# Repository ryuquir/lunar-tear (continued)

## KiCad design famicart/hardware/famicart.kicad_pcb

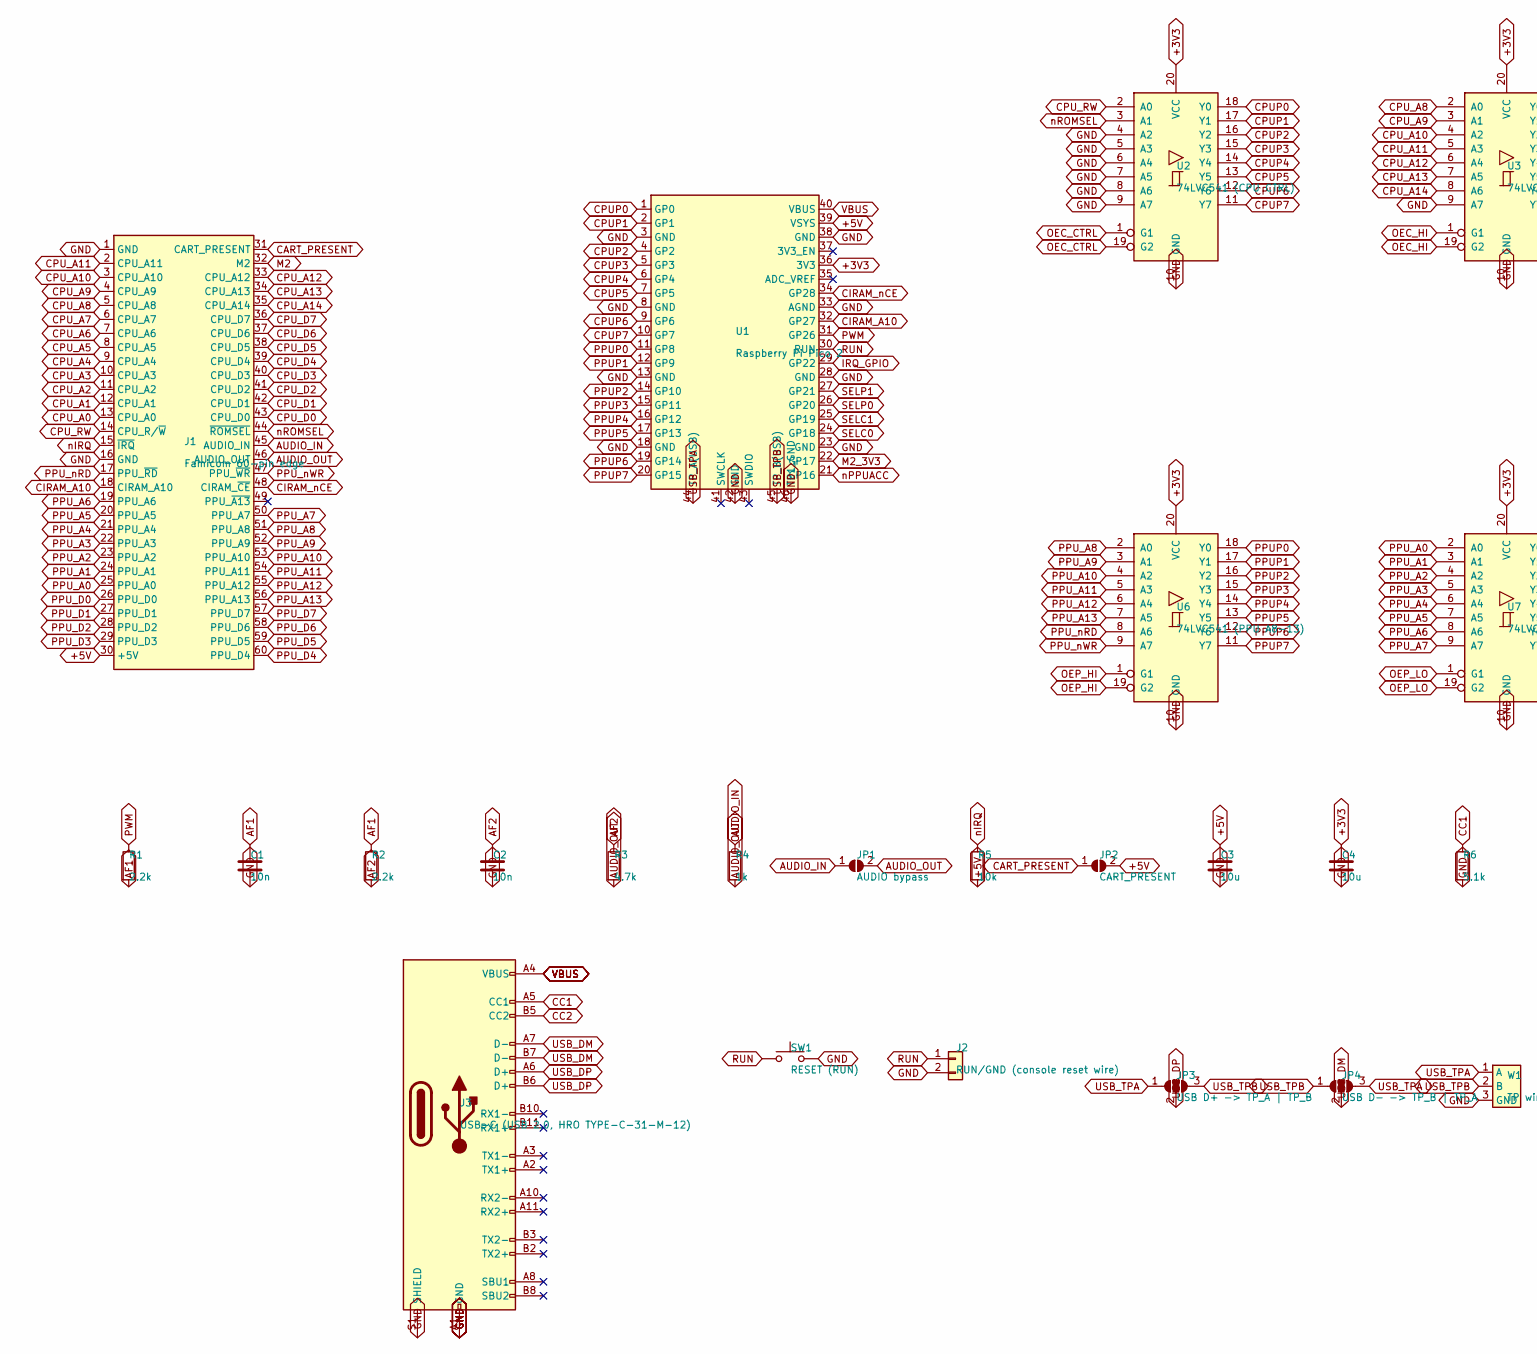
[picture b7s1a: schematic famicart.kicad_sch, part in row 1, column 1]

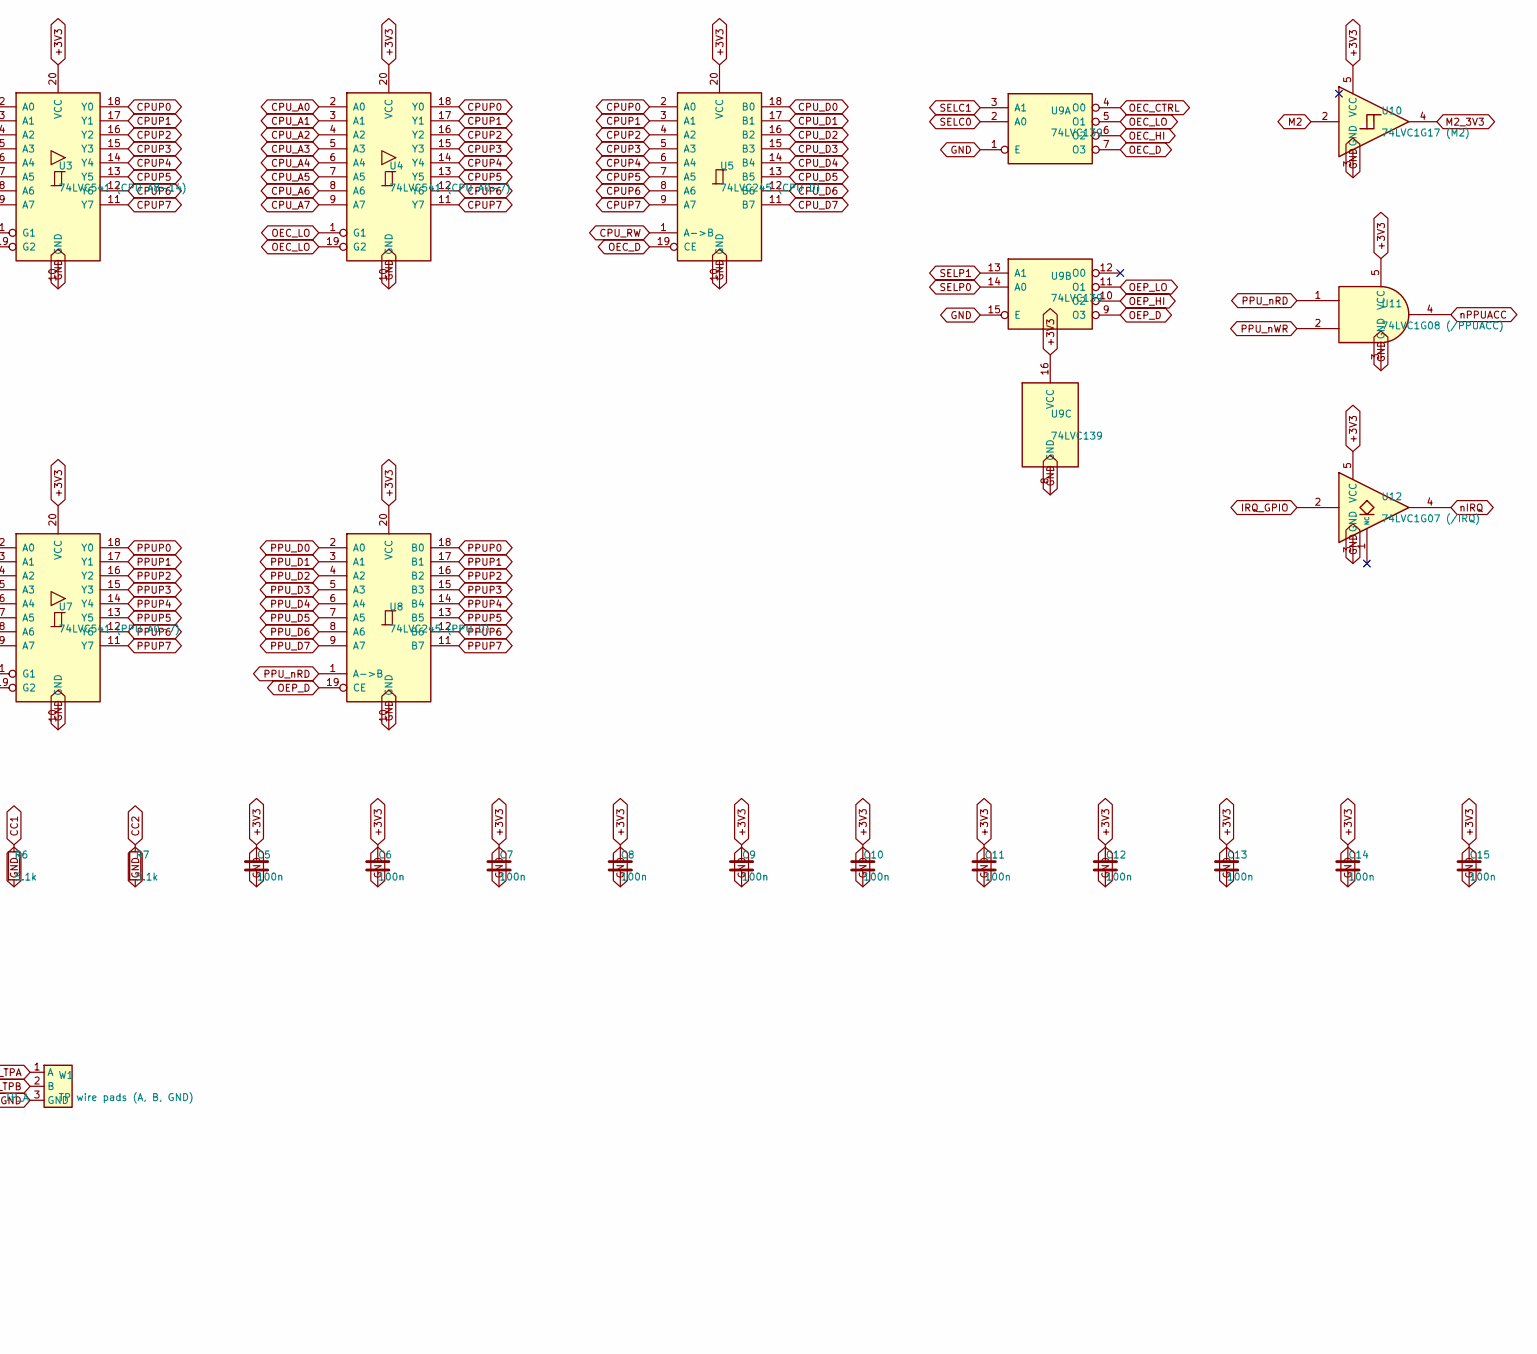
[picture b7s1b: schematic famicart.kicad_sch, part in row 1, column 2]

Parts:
C1, C2: 10n; C_0603_1608Metric
C3, C4: 10u; C_0805_2012Metric
C5, C6, C7, C8, C9, C10, C11, C12, C13, C14, C15: 100n; C_0603_1608Metric
J1: Famicom 60-pin edge; Famicom_CardEdge_60
J2: RUN/GND (console reset wire); PinHeader_1x02_P2.54mm_Vertical
J3: USB-C (USB 2.0, HRO TYPE-C-31-M-12); USB_C_Receptacle_HRO_TYPE-C-31-M-12
JP1: AUDIO bypass; SolderJumper-2_P1.3mm_Open_RoundedPad1.0x1.5mm
JP2: CART_PRESENT; SolderJumper-2_P1.3mm_Open_RoundedPad1.0x1.5mm
JP3: USB D+ -> TP_A | TP_B; SolderJumper-3_P1.6mm_Open
JP4: USB D- -> TP_B | TP_A; SolderJumper-3_P1.6mm_Open
R1, R2: 2.2k; R_0603_1608Metric
R3: 4.7k; R_0603_1608Metric
R4: 1k; R_0603_1608Metric
R5: 10k; R_0603_1608Metric
R6, R7: 5.1k; R_0603_1608Metric
SW1: RESET (RUN); SW_SPST_TL3342
U1: Raspberry Pi Pico 2; RPi_Pico_SMD
U2: 74LVC541 (CPU CTRL); TSSOP-20_4.4x6.5mm_P0.65mm
U3: 74LVC541 (CPU A8-14); TSSOP-20_4.4x6.5mm_P0.65mm
U4: 74LVC541 (CPU A0-7); TSSOP-20_4.4x6.5mm_P0.65mm
U5: 74LVC245 (CPU D); TSSOP-20_4.4x6.5mm_P0.65mm
U6: 74LVC541 (PPU A8-13); TSSOP-20_4.4x6.5mm_P0.65mm
U7: 74LVC541 (PPU A0-7); TSSOP-20_4.4x6.5mm_P0.65mm
U8: 74LVC245 (PPU D); TSSOP-20_4.4x6.5mm_P0.65mm
U9: 74LVC139; TSSOP-16_4.4x5mm_P0.65mm
U10: 74LVC1G17 (M2); SOT-23-5
U11: 74LVC1G08 (/PPUACC); SOT-23-5
U12: 74LVC1G07 (/IRQ); SOT-23-5
W1: TP wire pads (A, B, GND); WirePads_1x3

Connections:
+3V3: C4.1, C5.1, C6.1, C7.1, C8.1, C9.1, C10.1, C11.1, C12.1, C13.1, C14.1, C15.1, U1.36 (3V3), U2.20 (VCC), U3.20 (VCC), U4.20 (VCC), U5.20 (VCC), U6.20 (VCC), U7.20 (VCC), U8.20 (VCC), U9.16 (VCC), U10.5 (VCC), U11.5 (VCC), U12.5 (VCC)
+5V: C3.1, J1.30 (+5V), JP2.2 (B), R5.2, U1.39 (VSYS)
AF1: C1.1, R1.2, R2.1
AF2: C2.1, R2.2, R3.1
AUDIO_IN: J1.45 (AUDIO_IN), JP1.1 (A), R4.1
AUDIO_OUT: J1.46 (AUDIO_OUT), JP1.2 (B), R3.2, R4.2
CART_PRESENT: J1.31 (CART_PRESENT), JP2.1 (A)
CC1: J3.A5 (CC1), R6.1
CC2: J3.B5 (CC2), R7.1
CIRAM_A10: J1.18 (CIRAM_A10), U1.32 (GP27)
CIRAM_nCE: J1.48 (CIRAM_~CE), U1.34 (GP28)
CPUP0: U1.1 (GP0), U2.18 (Y0), U3.18 (Y0), U4.18 (Y0), U5.2 (A0)
CPUP1: U1.2 (GP1), U2.17 (Y1), U3.17 (Y1), U4.17 (Y1), U5.3 (A1)
CPUP2: U1.4 (GP2), U2.16 (Y2), U3.16 (Y2), U4.16 (Y2), U5.4 (A2)
CPUP3: U1.5 (GP3), U2.15 (Y3), U3.15 (Y3), U4.15 (Y3), U5.5 (A3)
CPUP4: U1.6 (GP4), U2.14 (Y4), U3.14 (Y4), U4.14 (Y4), U5.6 (A4)
CPUP5: U1.7 (GP5), U2.13 (Y5), U3.13 (Y5), U4.13 (Y5), U5.7 (A5)
CPUP6: U1.9 (GP6), U2.12 (Y6), U3.12 (Y6), U4.12 (Y6), U5.8 (A6)
CPUP7: U1.10 (GP7), U2.11 (Y7), U3.11 (Y7), U4.11 (Y7), U5.9 (A7)
CPU_A0: J1.13 (CPU_A0), U4.2 (A0)
CPU_A1: J1.12 (CPU_A1), U4.3 (A1)
CPU_A2: J1.11 (CPU_A2), U4.4 (A2)
CPU_A3: J1.10 (CPU_A3), U4.5 (A3)
CPU_A4: J1.9 (CPU_A4), U4.6 (A4)
CPU_A5: J1.8 (CPU_A5), U4.7 (A5)
CPU_A6: J1.7 (CPU_A6), U4.8 (A6)
CPU_A7: J1.6 (CPU_A7), U4.9 (A7)
CPU_A8: J1.5 (CPU_A8), U3.2 (A0)
CPU_A9: J1.4 (CPU_A9), U3.3 (A1)
CPU_A10: J1.3 (CPU_A10), U3.4 (A2)
CPU_A11: J1.2 (CPU_A11), U3.5 (A3)
CPU_A12: J1.33 (CPU_A12), U3.6 (A4)
CPU_A13: J1.34 (CPU_A13), U3.7 (A5)
CPU_A14: J1.35 (CPU_A14), U3.8 (A6)
CPU_D0: J1.43 (CPU_D0), U5.18 (B0)
CPU_D1: J1.42 (CPU_D1), U5.17 (B1)
CPU_D2: J1.41 (CPU_D2), U5.16 (B2)
CPU_D3: J1.40 (CPU_D3), U5.15 (B3)
CPU_D4: J1.39 (CPU_D4), U5.14 (B4)
CPU_D5: J1.38 (CPU_D5), U5.13 (B5)
CPU_D6: J1.37 (CPU_D6), U5.12 (B6)
CPU_D7: J1.36 (CPU_D7), U5.11 (B7)
CPU_RW: J1.14 (CPU_R/~W), U2.2 (A0), U5.1 (A->B)
GND: C1.2, C2.2, C3.2, C4.2, C5.2, C6.2, C7.2, C8.2, C9.2, C10.2, C11.2, C12.2, C13.2, C14.2, C15.2, J1.1 (GND), J1.16 (GND), J2.2, J3.A1 (GND), J3.A12 (GND), J3.B1 (GND), J3.B12 (GND), J3.S1 (SHIELD), R6.2, R7.2, SW1.2, U1.3 (GND), U1.8 (GND), U1.13 (GND), U1.18 (GND), U1.23 (GND), U1.28 (GND), U1.33 (AGND), U1.38 (GND), U1.42 (GND), U1.46 (TP1_GND), U2.4 (A2), U2.5 (A3), U2.6 (A4), U2.7 (A5), U2.8 (A6), U2.9 (A7), U2.10 (GND), U3.9 (A7), U3.10 (GND), U4.10 (GND), U5.10 (GND), U6.10 (GND), U7.10 (GND), U8.10 (GND), U9.1 (E), U9.8 (GND), U9.15 (E), U10.3 (GND), U11.3 (GND), U12.3 (GND), W1.3 (GND)
IRQ_GPIO: U1.29 (GP22), U12.2
M2: J1.32 (M2), U10.2
M2_3V3: U1.22 (GP17), U10.4
OEC_CTRL: U2.1 (G1), U2.19 (G2), U9.4 (O0)
OEC_D: U5.19 (CE), U9.7 (O3)
OEC_HI: U3.1 (G1), U3.19 (G2), U9.6 (O2)
OEC_LO: U4.1 (G1), U4.19 (G2), U9.5 (O1)
OEP_D: U8.19 (CE), U9.9 (O3)
OEP_HI: U6.1 (G1), U6.19 (G2), U9.10 (O2)
OEP_LO: U7.1 (G1), U7.19 (G2), U9.11 (O1)
PPUP0: U1.11 (GP8), U6.18 (Y0), U7.18 (Y0), U8.18 (B0)
PPUP1: U1.12 (GP9), U6.17 (Y1), U7.17 (Y1), U8.17 (B1)
PPUP2: U1.14 (GP10), U6.16 (Y2), U7.16 (Y2), U8.16 (B2)
PPUP3: U1.15 (GP11), U6.15 (Y3), U7.15 (Y3), U8.15 (B3)
PPUP4: U1.16 (GP12), U6.14 (Y4), U7.14 (Y4), U8.14 (B4)
PPUP5: U1.17 (GP13), U6.13 (Y5), U7.13 (Y5), U8.13 (B5)
PPUP6: U1.19 (GP14), U6.12 (Y6), U7.12 (Y6), U8.12 (B6)
PPUP7: U1.20 (GP15), U6.11 (Y7), U7.11 (Y7), U8.11 (B7)
PPU_A0: J1.25 (PPU_A0), U7.2 (A0)
PPU_A1: J1.24 (PPU_A1), U7.3 (A1)
PPU_A2: J1.23 (PPU_A2), U7.4 (A2)
PPU_A3: J1.22 (PPU_A3), U7.5 (A3)
PPU_A4: J1.21 (PPU_A4), U7.6 (A4)
PPU_A5: J1.20 (PPU_A5), U7.7 (A5)
PPU_A6: J1.19 (PPU_A6), U7.8 (A6)
PPU_A7: J1.50 (PPU_A7), U7.9 (A7)
PPU_A8: J1.51 (PPU_A8), U6.2 (A0)
PPU_A9: J1.52 (PPU_A9), U6.3 (A1)
PPU_A10: J1.53 (PPU_A10), U6.4 (A2)
PPU_A11: J1.54 (PPU_A11), U6.5 (A3)
PPU_A12: J1.55 (PPU_A12), U6.6 (A4)
PPU_A13: J1.56 (PPU_A13), U6.7 (A5)
PPU_D0: J1.26 (PPU_D0), U8.2 (A0)
PPU_D1: J1.27 (PPU_D1), U8.3 (A1)
PPU_D2: J1.28 (PPU_D2), U8.4 (A2)
PPU_D3: J1.29 (PPU_D3), U8.5 (A3)
PPU_D4: J1.60 (PPU_D4), U8.6 (A4)
PPU_D5: J1.59 (PPU_D5), U8.7 (A5)
PPU_D6: J1.58 (PPU_D6), U8.8 (A6)
PPU_D7: J1.57 (PPU_D7), U8.9 (A7)
PPU_nRD: J1.17 (PPU_~RD), U6.8 (A6), U8.1 (A->B), U11.1
PPU_nWR: J1.47 (PPU_~WR), U6.9 (A7), U11.2
PWM: R1.1, U1.31 (GP26)
RUN: J2.1, SW1.1, U1.30 (RUN)
SELC0: U1.24 (GP18), U9.2 (A0)
SELC1: U1.25 (GP19), U9.3 (A1)
SELP0: U1.26 (GP20), U9.14 (A0)
SELP1: U1.27 (GP21), U9.13 (A1)
USB_DM: J3.A7 (D-), J3.B7 (D-), JP4.2 (C)
USB_DP: J3.A6 (D+), J3.B6 (D+), JP3.2 (C)
USB_TPA: JP3.1 (A), JP4.3 (B), U1.44 (TP_A(USB)), W1.1 (A)
USB_TPB: JP3.3 (B), JP4.1 (A), U1.45 (TP_B(USB)), W1.2 (B)
VBUS: J3.A4 (VBUS), J3.A9 (VBUS), J3.B4 (VBUS), J3.B9 (VBUS), U1.40 (VBUS)
nIRQ: J1.15 (~IRQ), R5.1, U12.4
nPPUACC: U1.21 (GP16), U11.4
nROMSEL: J1.44 (~ROMSEL), U2.3 (A1)

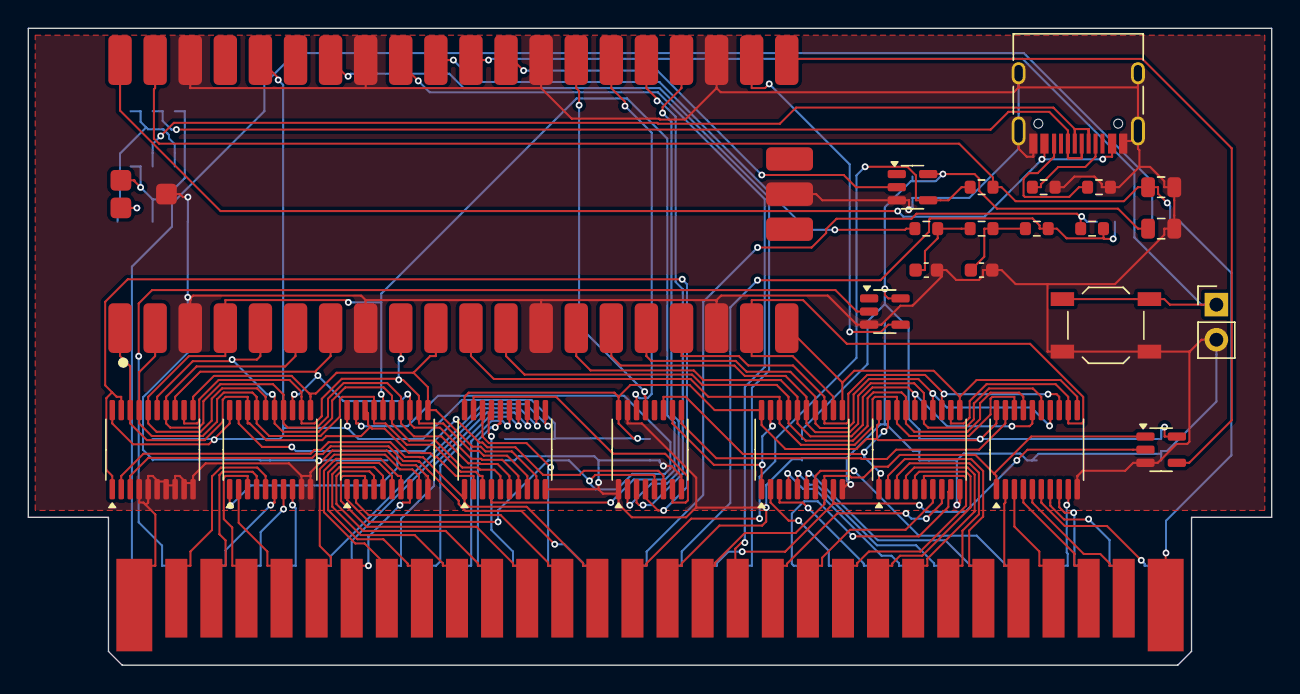
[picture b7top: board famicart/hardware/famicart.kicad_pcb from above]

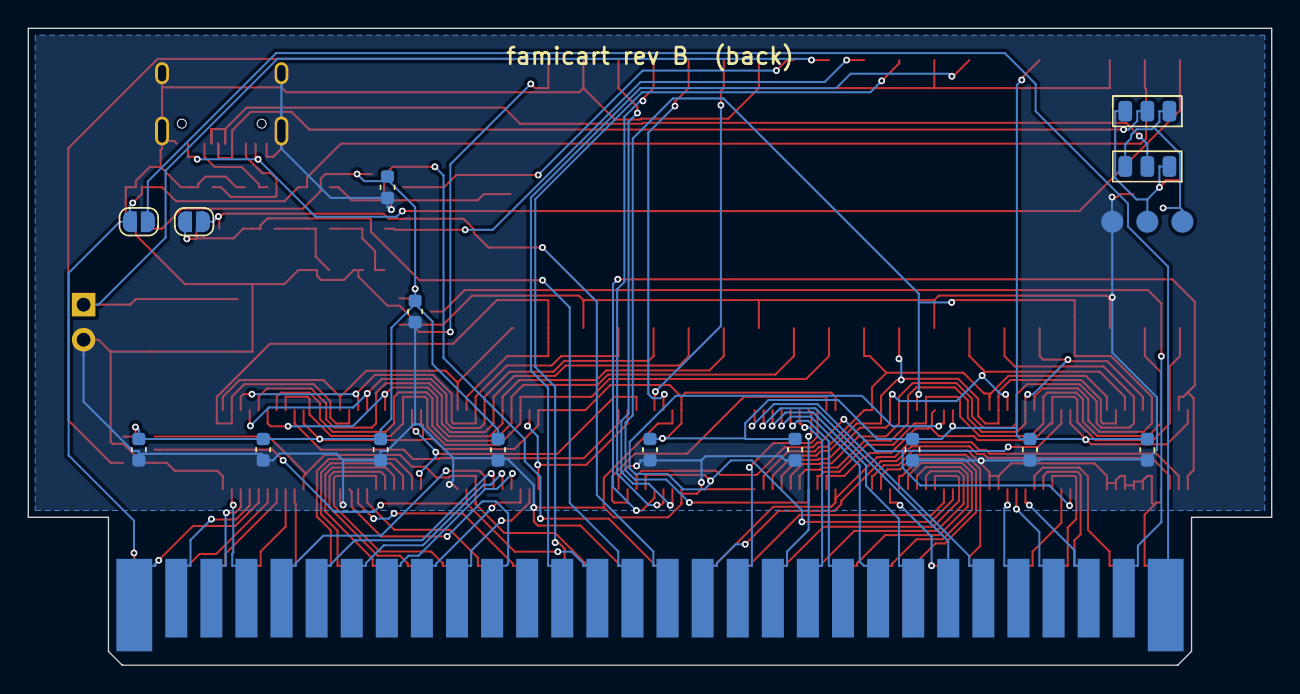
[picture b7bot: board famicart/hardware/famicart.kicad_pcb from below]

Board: 2 copper layers, 90.0 x 46.1 mm, 43 parts (16 on the bottom side), 100 nets.

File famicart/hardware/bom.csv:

Qty,Value,Footprint,References,Suggested part
1,Famicom 60-pin edge,Famicom_CardEdge_60,J1,"PCB card edge (gold fingers), no part"
1,Raspberry Pi Pico 2,RPi_Pico_SMD,U1,Raspberry Pi SC1631 (Pico 2) / Pico (RP2040) also fits
5,74LVC541,TSSOP-20_4.4x6.5mm_P0.65mm,U2 U3 U4 U6 U7,Nexperia 74LVC541APW (TSSOP-20)
2,74LVC245,TSSOP-20_4.4x6.5mm_P0.65mm,U5 U8,Nexperia 74LVC245APW (TSSOP-20)
1,74LVC139,TSSOP-16_4.4x5mm_P0.65mm,U9,Nexperia 74LVC139PW (TSSOP-16)
1,74LVC1G17,SOT-23-5,U10,Nexperia 74LVC1G17GW / TI SN74LVC1G17DBV
1,USB-C,USB_C_Receptacle_HRO_TYPE-C-31-M-12,J3,HRO TYPE-C-31-M-12 (16-pin USB 2.0 receptacle) or GCT USB4105-GF-A
2,5.1k,R_0603_1608Metric,R6 R7,0603 1% (USB-C CC pull-down)
1,USB D+ -> TP_A | TP_B,SolderJumper-3_P1.6mm_Open,JP3,"solder jumper, bridge after checking TP2/TP3"
1,USB D- -> TP_B | TP_A,SolderJumper-3_P1.6mm_Open,JP4,"solder jumper, bridge after checking TP2/TP3"
1,TP wire pads,WirePads_1x3,W1,no part (solder wires from Pico TP2/TP3/TP1 if hand-assembling)
1,RESET,SW_SPST_TL3342,SW1,E-Switch TL3342 / any 4.7x3.5 mm low-profile tactile
1,RUN/GND,PinHeader_1x02_P2.54mm_Vertical,J2,"2-pin 2.54 mm header (optional, wire to the console reset switch)"
1,74LVC1G08,SOT-23-5,U11,Nexperia 74LVC1G08GW / TI SN74LVC1G08DBV
1,74LVC1G07,SOT-23-5,U12,Nexperia 74LVC1G07GW / TI SN74LVC1G07DBV
2,2.2k,R_0603_1608Metric,R1 R2,0603 1%
1,4.7k,R_0603_1608Metric,R3,0603 1%
1,1k,R_0603_1608Metric,R4,0603 1%
1,10k,R_0603_1608Metric,R5,0603 1%
2,10n,C_0603_1608Metric,C1 C2,X7R 0603 50V
2,10u,C_0805_2012Metric,C3 C4,X5R 0805 10V
1,AUDIO bypass,SolderJumper-2_P1.3mm_Open_RoundedPad1.0x1.5mm,JP1,
1,CART_PRESENT,SolderJumper-2_P1.3mm_Open_RoundedPad1.0x1.5mm,JP2,
11,100n,C_0603_1608Metric,C5 C6 C7 C8 C9 C10 C11 C12 C13 C14 C15,X7R 0603 16V

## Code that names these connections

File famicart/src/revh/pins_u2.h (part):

/* Generated by tools/fw/gen_revh_pins.py from tools/pcb/design_revh.py -- do not edit; run the script again.
 * famicart rev H, U2: PPU bus (CHR, nametables, PPU write capture; PEV to U3).
 * RP2350B (QFN-80) with U12 (W25Q128JVSIQ, 16 MB) on QSPI CS0, its own 12 MHz crystal, LED D22 on LED2.
 * SWCLK (pin 33) SWCLK2, SWDIO (pin 34) SWDIO2, RUN (pin 35) nRST, USB pins 66 / 67 open.
 * "pin" below is the QFN-80 pin (design_revd.GPIO_PIN, checked against the datasheet). Include exactly one
 * pins_u<N>.h per program: the names repeat across chips with other numbers. */
#ifndef FAMICART_REVH_PINS_U2_H
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#define REVH_IS_HUB 0

/* ---- every connected GPIO: pin, net, what else is on the net */
#define PIN_PA0       0  /* pin 77  PA0: U5; RN10 1k -> PPU_A0 (finger 25) */
#define PIN_PA1       1  /* pin 78  PA1: U5; RN9 1k -> PPU_A1 (finger 24) */
#define PIN_PA2       2  /* pin 79  PA2: U5; RN9 1k -> PPU_A2 (finger 23) */
#define PIN_PA3       3  /* pin 80  PA3: U5; RN8 1k -> PPU_A3 (finger 22) */
#define PIN_PA4       4  /* pin  1  PA4: U5; RN8 1k -> PPU_A4 (finger 21) */
#define PIN_PA5       5  /* pin  2  PA5: U5; RN7 1k -> PPU_A5 (finger 20) */
#define PIN_PA6       6  /* pin  3  PA6: U5; RN7 1k -> PPU_A6 (finger 19) */
#define PIN_PA7       7  /* pin  4  PA7: U5; RN8 1k -> PPU_A7 (finger 50) */
#define PIN_PA8       8  /* pin  6  PA8: U5; RN8 1k -> PPU_A8 (finger 51) */
#define PIN_PA9       9  /* pin  7  PA9: U5; RN9 1k -> PPU_A9 (finger 52) */
#define PIN_PA10     10  /* pin  8  PA10: U3 U5; RN9 1k -> PPU_A10 (finger 53) */
#define PIN_PA11     11  /* pin  9  PA11: U3 U5; RN10 1k -> PPU_A11 (finger 54) */
#define PIN_PA12     12  /* pin 11  PA12: U3 U5; RN10 1k -> PPU_A12 (finger 55) */
#define PIN_PA13     13  /* pin 12  PA13: U3 U5; RN10 1k -> PPU_A13 (finger 56) */
#define PIN_PD0      14  /* pin 13  PD0: RN11 680 x2 -> PPU_D0 (finger 26) */
#define PIN_PD1      15  /* pin 14  PD1: RN11 680 x2 -> PPU_D1 (finger 27) */
#define PIN_PD2      16  /* pin 16  PD2: RN12 680 x2 -> PPU_D2 (finger 28) */
#define PIN_PD3      17  /* pin 17  PD3: RN12 680 x2 -> PPU_D3 (finger 29) */
#define PIN_PD4      18  /* pin 18  PD4: RN16 680 x2 -> PPU_D4 (finger 60) */
#define PIN_PD5      19  /* pin 19  PD5: RN16 680 x2 -> PPU_D5 (finger 59) */
#define PIN_PD6      20  /* pin 20  PD6: RN15 680 x2 -> PPU_D6 (finger 58) */
#define PIN_PD7      21  /* pin 21  PD7: RN15 680 x2 -> PPU_D7 (finger 57) */
#define PIN_RD_D     22  /* pin 22  RD_D: U5; RN17 1k -> PPU_nRD (finger 17) */
#define PIN_PEV      23  /* pin 23  PEV: U3 */
#define PIN_P_WE     24  /* pin 25  P_WE: U5; RN32 1k -> PPU_nWE (finger 47) */
#define PIN_PWS_D    26  /* pin 27  PWS_D: U5; R28 2.2k -> +3V3; R29 2.2k -> +3V3; Q6 drain (gate PWE_G) */
#define PIN_PLINK_B  27  /* pin 28  PLINK_B: RN26 1k x2 -> PLINK_F */
#define PIN_LINK_B   28  /* pin 36  LINK_B: RN22 1k x4 -> LINK */
#define PIN_WL_CK    29  /* pin 37  WL_CK: U1 U5 U6 */
#define PIN_WL_D0    30  /* pin 38  WL_D0: U1 U5 U6 */
#define PIN_WL_D1    31  /* pin 39  WL_D1: U1 U5 U6 */
#define PIN_XH2_2_CK 32  /* pin 40  XH2_2_CK: U6 */
#define PIN_XH2_2_D0 33  /* pin 42  XH2_2_D0: U6 */
#define PIN_XH2_2_D1 34  /* pin 43  XH2_2_D1: U6 */
#define PIN_XH2_H_CK 35  /* pin 44  XH2_H_CK: U6 */
#define PIN_XH2_H_D0 36  /* pin 45  XH2_H_D0: U6 */
#define PIN_XH2_H_D1 37  /* pin 46  XH2_H_D1: U6 */
#define PIN_X25_2_CK 38  /* pin 47  X25_2_CK: U5 */
#define PIN_X25_2_D0 39  /* pin 48  X25_2_D0: U5 */
#define PIN_X25_2_D1 40  /* pin 49  X25_2_D1: U5 */
#define PIN_X25_5_CK 41  /* pin 52  X25_5_CK: U5 */
#define PIN_X25_5_D0 42  /* pin 53  X25_5_D0: U5 */
#define PIN_X25_5_D1 43  /* pin 54  X25_5_D1: U5 */
#define PIN_VSEL_S   44  /* pin 55  VSEL_S: all other chips; R35 100k -> GND; Q7 gate (drain VSEL_D) */
#define PIN_LED2     45  /* pin 56  LED2: R4 2.2k -> LED2_A */

/* ---- GPIOs with no net (reset state: input buffer off, pad pull-down, isolated): 25, 46, 47 */
#define REVH_UNCONNECTED_MASK 0xc00002000000ull
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
/* ---- consecutive groups for PIO programs (in / out / set / side-set base and count). The PIO window is the
 * GPIOBASE (0 or 16) whose 32 GPIOs hold the whole group; with GPIOBASE 16, `wait gpio` numbers are relative. */
/* PPU_BUS: PA0..RD_D, PPU bus capture: A0-13, D0-7, /RD; PIO window GPIOBASE 0 */
#define PIN_PPU_BUS_BASE  0
#define PIN_PPU_BUS_COUNT 23
_Static_assert(PIN_PA0 == PIN_PPU_BUS_BASE + 0 && PIN_PA1 == PIN_PPU_BUS_BASE + 1 &&
               PIN_PA2 == PIN_PPU_BUS_BASE + 2 && PIN_PA3 == PIN_PPU_BUS_BASE + 3 &&
               PIN_PA4 == PIN_PPU_BUS_BASE + 4 && PIN_PA5 == PIN_PPU_BUS_BASE + 5 &&
               PIN_PA6 == PIN_PPU_BUS_BASE + 6 && PIN_PA7 == PIN_PPU_BUS_BASE + 7 &&
               PIN_PA8 == PIN_PPU_BUS_BASE + 8 && PIN_PA9 == PIN_PPU_BUS_BASE + 9 &&
               PIN_PA10 == PIN_PPU_BUS_BASE + 10 && PIN_PA11 == PIN_PPU_BUS_BASE + 11 &&
               PIN_PA12 == PIN_PPU_BUS_BASE + 12 && PIN_PA13 == PIN_PPU_BUS_BASE + 13 &&
               PIN_PD0 == PIN_PPU_BUS_BASE + 14 && PIN_PD1 == PIN_PPU_BUS_BASE + 15 &&
               PIN_PD2 == PIN_PPU_BUS_BASE + 16 && PIN_PD3 == PIN_PPU_BUS_BASE + 17 &&
               PIN_PD4 == PIN_PPU_BUS_BASE + 18 && PIN_PD5 == PIN_PPU_BUS_BASE + 19 &&
               PIN_PD6 == PIN_PPU_BUS_BASE + 20 && PIN_PD7 == PIN_PPU_BUS_BASE + 21 &&
               PIN_RD_D == PIN_PPU_BUS_BASE + 22,
               "PPU_BUS: PA0..RD_D must be consecutive GPIOs");
/* PA: PA0..PA13, to PPU_A0..PPU_A13 through RN7, RN8, RN9, RN10 (1k each); PIO window GPIOBASE 0 */
#define PIN_PA_BASE  0
#define PIN_PA_COUNT 14
_Static_assert(PIN_PA0 == PIN_PA_BASE + 0 && PIN_PA1 == PIN_PA_BASE + 1 && PIN_PA2 == PIN_PA_BASE + 2 &&
               PIN_PA3 == PIN_PA_BASE + 3 && PIN_PA4 == PIN_PA_BASE + 4 && PIN_PA5 == PIN_PA_BASE + 5 &&
               PIN_PA6 == PIN_PA_BASE + 6 && PIN_PA7 == PIN_PA_BASE + 7 && PIN_PA8 == PIN_PA_BASE + 8 &&
               PIN_PA9 == PIN_PA_BASE + 9 && PIN_PA10 == PIN_PA_BASE + 10 && PIN_PA11 == PIN_PA_BASE + 11 &&
               PIN_PA12 == PIN_PA_BASE + 12 && PIN_PA13 == PIN_PA_BASE + 13,
               "PA: PA0..PA13 must be consecutive GPIOs");
/* PD: PD0..PD7, to PPU_D0..PPU_D7 through RN11, RN12, RN15, RN16 (680 x2 each); PIO window GPIOBASE 0 */
#define PIN_PD_BASE  14
#define PIN_PD_COUNT 8
_Static_assert(PIN_PD0 == PIN_PD_BASE + 0 && PIN_PD1 == PIN_PD_BASE + 1 && PIN_PD2 == PIN_PD_BASE + 2 &&
               PIN_PD3 == PIN_PD_BASE + 3 && PIN_PD4 == PIN_PD_BASE + 4 && PIN_PD5 == PIN_PD_BASE + 5 &&
               PIN_PD6 == PIN_PD_BASE + 6 && PIN_PD7 == PIN_PD_BASE + 7,
               "PD: PD0..PD7 must be consecutive GPIOs");
/* WL: WL_CK..WL_D1, WLINK received by this chip (U1 drives clock, data 0, data 1); PIO window GPIOBASE 0 or 16 */
#define PIN_WL_BASE  29
#define PIN_WL_COUNT 3
_Static_assert(PIN_WL_CK == PIN_WL_BASE + 0 && PIN_WL_D0 == PIN_WL_BASE + 1 && PIN_WL_D1 == PIN_WL_BASE + 2,
               "WL: WL_CK..WL_D1 must be consecutive GPIOs");
/* XH2_2: XH2_2_CK..XH2_2_D1, XLINK-H2 sent by this chip (U2 drives clock, data 0, data 1); PIO window GPIOBASE 16 */
#define PIN_XH2_2_BASE  32
#define PIN_XH2_2_COUNT 3
_Static_assert(PIN_XH2_2_CK == PIN_XH2_2_BASE + 0 && PIN_XH2_2_D0 == PIN_XH2_2_BASE + 1 &&
               PIN_XH2_2_D1 == PIN_XH2_2_BASE + 2,
               "XH2_2: XH2_2_CK..XH2_2_D1 must be consecutive GPIOs");
#define PIN_XH2_TX_BASE  PIN_XH2_2_BASE
#define PIN_XH2_TX_COUNT PIN_XH2_2_COUNT
/* XH2_H: XH2_H_CK..XH2_H_D1, XLINK-H2 received by this chip (U6 drives clock, data 0, data 1); PIO window GPIOBASE 16 */
#define PIN_XH2_H_BASE  35
#define PIN_XH2_H_COUNT 3
_Static_assert(PIN_XH2_H_CK == PIN_XH2_H_BASE + 0 && PIN_XH2_H_D0 == PIN_XH2_H_BASE + 1 &&
               PIN_XH2_H_D1 == PIN_XH2_H_BASE + 2,
               "XH2_H: XH2_H_CK..XH2_H_D1 must be consecutive GPIOs");
#define PIN_XH2_RX_BASE  PIN_XH2_H_BASE
#define PIN_XH2_RX_COUNT PIN_XH2_H_COUNT
/* X25_2: X25_2_CK..X25_2_D1, XLINK-25 sent by this chip (U2 drives clock, data 0, data 1); PIO window GPIOBASE 16 */
#define PIN_X25_2_BASE  38
#define PIN_X25_2_COUNT 3
_Static_assert(PIN_X25_2_CK == PIN_X25_2_BASE + 0 && PIN_X25_2_D0 == PIN_X25_2_BASE + 1 &&
               PIN_X25_2_D1 == PIN_X25_2_BASE + 2,
               "X25_2: X25_2_CK..X25_2_D1 must be consecutive GPIOs");
#define PIN_X25_TX_BASE  PIN_X25_2_BASE
#define PIN_X25_TX_COUNT PIN_X25_2_COUNT
/* X25_5: X25_5_CK..X25_5_D1, XLINK-25 received by this chip (U5 drives clock, data 0, data 1); PIO window GPIOBASE 16 */
#define PIN_X25_5_BASE  41
#define PIN_X25_5_COUNT 3
_Static_assert(PIN_X25_5_CK == PIN_X25_5_BASE + 0 && PIN_X25_5_D0 == PIN_X25_5_BASE + 1 &&
               PIN_X25_5_D1 == PIN_X25_5_BASE + 2,
               "X25_5: X25_5_CK..X25_5_D1 must be consecutive GPIOs");
#define PIN_X25_RX_BASE  PIN_X25_5_BASE
#define PIN_X25_RX_COUNT PIN_X25_5_COUNT

/* ---- names shared by every chip */
#define PIN_LED PIN_LED2
#define PIN_LINK PIN_LINK_B       /* 250 ohm to the common LINK (U1-U6) */

#endif /* FAMICART_REVH_PINS_U2_H */

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
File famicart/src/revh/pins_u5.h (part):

/* Generated by tools/fw/gen_revh_pins.py from tools/pcb/design_revh.py -- do not edit; run the script again.
 * famicart rev H, U5: PPU-bus extension (permanent), XLINK to U2 and U9, IRQ5.
 * RP2350B (QFN-80) with U15 (W25Q128JVSIQ, 16 MB) on QSPI CS0, its own 12 MHz crystal, LED D25 on LED5.
 * SWCLK (pin 33) SWCLK5, SWDIO (pin 34) SWDIO5, RUN (pin 35) nRST, USB pins 66 / 67 open.
 * "pin" below is the QFN-80 pin (design_revd.GPIO_PIN, checked against the datasheet). Include exactly one
 * pins_u<N>.h per program: the names repeat across chips with other numbers. */
#ifndef FAMICART_REVH_PINS_U5_H
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
#define REVH_CHIP_5 1
#define REVH_CHIP 5
#define REVH_ROLE "ppu-ext"
#define REVH_IS_HUB 0

/* ---- every connected GPIO: pin, net, what else is on the net */
#define PIN_PA0       0  /* pin 77  PA0: U2; RN10 1k -> PPU_A0 (finger 25) */
#define PIN_PA1       1  /* pin 78  PA1: U2; RN9 1k -> PPU_A1 (finger 24) */
#define PIN_PA2       2  /* pin 79  PA2: U2; RN9 1k -> PPU_A2 (finger 23) */
#define PIN_PA3       3  /* pin 80  PA3: U2; RN8 1k -> PPU_A3 (finger 22) */
#define PIN_PA4       4  /* pin  1  PA4: U2; RN8 1k -> PPU_A4 (finger 21) */
#define PIN_PA5       5  /* pin  2  PA5: U2; RN7 1k -> PPU_A5 (finger 20) */
#define PIN_PA6       6  /* pin  3  PA6: U2; RN7 1k -> PPU_A6 (finger 19) */
#define PIN_PA7       7  /* pin  4  PA7: U2; RN8 1k -> PPU_A7 (finger 50) */
#define PIN_PA8       8  /* pin  6  PA8: U2; RN8 1k -> PPU_A8 (finger 51) */
#define PIN_PA9       9  /* pin  7  PA9: U2; RN9 1k -> PPU_A9 (finger 52) */
#define PIN_PA10     10  /* pin  8  PA10: U2 U3; RN9 1k -> PPU_A10 (finger 53) */
#define PIN_PA11     11  /* pin  9  PA11: U2 U3; RN10 1k -> PPU_A11 (finger 54) */
#define PIN_PA12     12  /* pin 11  PA12: U2 U3; RN10 1k -> PPU_A12 (finger 55) */
#define PIN_PA13     13  /* pin 12  PA13: U2 U3; RN10 1k -> PPU_A13 (finger 56) */
#define PIN_YD0      14  /* pin 13  YD0: RN27 680 x2 -> PPU_D0 (finger 26) */
#define PIN_YD1      15  /* pin 14  YD1: RN27 680 x2 -> PPU_D1 (finger 27) */
#define PIN_YD2      16  /* pin 16  YD2: RN28 680 x2 -> PPU_D2 (finger 28) */
#define PIN_YD3      17  /* pin 17  YD3: RN28 680 x2 -> PPU_D3 (finger 29) */
#define PIN_YD4      18  /* pin 18  YD4: RN30 680 x2 -> PPU_D4 (finger 60) */
#define PIN_YD5      19  /* pin 19  YD5: RN30 680 x2 -> PPU_D5 (finger 59) */
#define PIN_YD6      20  /* pin 20  YD6: RN29 680 x2 -> PPU_D6 (finger 58) */
#define PIN_YD7      21  /* pin 21  YD7: RN29 680 x2 -> PPU_D7 (finger 57) */
#define PIN_RD_D     22  /* pin 22  RD_D: U2; RN17 1k -> PPU_nRD (finger 17) */
#define PIN_P_WE     24  /* pin 25  P_WE: U2; RN32 1k -> PPU_nWE (finger 47) */
#define PIN_PWS_D    26  /* pin 27  PWS_D: U2; R28 2.2k -> +3V3; R29 2.2k -> +3V3; Q6 drain (gate PWE_G) */
#define PIN_PLINK_E  27  /* pin 28  PLINK_E: RN26 1k x2 -> PLINK_F */
#define PIN_LINK_E   28  /* pin 36  LINK_E: RN23 1k x4 -> LINK */
#define PIN_WL_CK    29  /* pin 37  WL_CK: U1 U2 U6 */
#define PIN_WL_D0    30  /* pin 38  WL_D0: U1 U2 U6 */
#define PIN_WL_D1    31  /* pin 39  WL_D1: U1 U2 U6 */
#define PIN_X59_5_CK 32  /* pin 40  X59_5_CK: U9 */
#define PIN_X59_5_D0 33  /* pin 42  X59_5_D0: U9 */
#define PIN_X59_5_D1 34  /* pin 43  X59_5_D1: U9 */
#define PIN_X59_9_CK 35  /* pin 44  X59_9_CK: U9 */
#define PIN_X59_9_D0 36  /* pin 45  X59_9_D0: U9 */
#define PIN_X59_9_D1 37  /* pin 46  X59_9_D1: U9 */
#define PIN_X25_5_CK 38  /* pin 47  X25_5_CK: U2 */
#define PIN_X25_5_D0 39  /* pin 48  X25_5_D0: U2 */
#define PIN_X25_5_D1 40  /* pin 49  X25_5_D1: U2 */
#define PIN_X25_2_CK 41  /* pin 52  X25_2_CK: U2 */
#define PIN_X25_2_D0 42  /* pin 53  X25_2_D0: U2 */
#define PIN_X25_2_D1 43  /* pin 54  X25_2_D1: U2 */
#define PIN_IRQ5     44  /* pin 55  IRQ5: U3 */
#define PIN_VSEL_S   45  /* pin 56  VSEL_S: all other chips; R35 100k -> GND; Q7 gate (drain VSEL_D) */
#define PIN_LED5     46  /* pin 57  LED5: R12 2.2k -> LED5_A */

/* ---- GPIOs with no net (reset state: input buffer off, pad pull-down, isolated): 23, 25, 47 */
#define REVH_UNCONNECTED_MASK 0x800002800000ull
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
/* ---- consecutive groups for PIO programs (in / out / set / side-set base and count). The PIO window is the
 * GPIOBASE (0 or 16) whose 32 GPIOs hold the whole group; with GPIOBASE 16, `wait gpio` numbers are relative. */
/* PPU_BUS: PA0..RD_D, PPU bus capture: A0-13, D0-7, /RD; PIO window GPIOBASE 0 */
#define PIN_PPU_BUS_BASE  0
#define PIN_PPU_BUS_COUNT 23
_Static_assert(PIN_PA0 == PIN_PPU_BUS_BASE + 0 && PIN_PA1 == PIN_PPU_BUS_BASE + 1 &&
               PIN_PA2 == PIN_PPU_BUS_BASE + 2 && PIN_PA3 == PIN_PPU_BUS_BASE + 3 &&
               PIN_PA4 == PIN_PPU_BUS_BASE + 4 && PIN_PA5 == PIN_PPU_BUS_BASE + 5 &&
               PIN_PA6 == PIN_PPU_BUS_BASE + 6 && PIN_PA7 == PIN_PPU_BUS_BASE + 7 &&
               PIN_PA8 == PIN_PPU_BUS_BASE + 8 && PIN_PA9 == PIN_PPU_BUS_BASE + 9 &&
               PIN_PA10 == PIN_PPU_BUS_BASE + 10 && PIN_PA11 == PIN_PPU_BUS_BASE + 11 &&
               PIN_PA12 == PIN_PPU_BUS_BASE + 12 && PIN_PA13 == PIN_PPU_BUS_BASE + 13 &&
               PIN_YD0 == PIN_PPU_BUS_BASE + 14 && PIN_YD1 == PIN_PPU_BUS_BASE + 15 &&
               PIN_YD2 == PIN_PPU_BUS_BASE + 16 && PIN_YD3 == PIN_PPU_BUS_BASE + 17 &&
               PIN_YD4 == PIN_PPU_BUS_BASE + 18 && PIN_YD5 == PIN_PPU_BUS_BASE + 19 &&
               PIN_YD6 == PIN_PPU_BUS_BASE + 20 && PIN_YD7 == PIN_PPU_BUS_BASE + 21 &&
               PIN_RD_D == PIN_PPU_BUS_BASE + 22,
               "PPU_BUS: PA0..RD_D must be consecutive GPIOs");
/* PA: PA0..PA13, to PPU_A0..PPU_A13 through RN7, RN8, RN9, RN10 (1k each); PIO window GPIOBASE 0 */
#define PIN_PA_BASE  0
#define PIN_PA_COUNT 14
_Static_assert(PIN_PA0 == PIN_PA_BASE + 0 && PIN_PA1 == PIN_PA_BASE + 1 && PIN_PA2 == PIN_PA_BASE + 2 &&
               PIN_PA3 == PIN_PA_BASE + 3 && PIN_PA4 == PIN_PA_BASE + 4 && PIN_PA5 == PIN_PA_BASE + 5 &&
               PIN_PA6 == PIN_PA_BASE + 6 && PIN_PA7 == PIN_PA_BASE + 7 && PIN_PA8 == PIN_PA_BASE + 8 &&
               PIN_PA9 == PIN_PA_BASE + 9 && PIN_PA10 == PIN_PA_BASE + 10 && PIN_PA11 == PIN_PA_BASE + 11 &&
               PIN_PA12 == PIN_PA_BASE + 12 && PIN_PA13 == PIN_PA_BASE + 13,
               "PA: PA0..PA13 must be consecutive GPIOs");
/* YD: YD0..YD7, to PPU_D0..PPU_D7 through RN27, RN28, RN29, RN30 (680 x2 each); PIO window GPIOBASE 0 */
#define PIN_YD_BASE  14
#define PIN_YD_COUNT 8
_Static_assert(PIN_YD0 == PIN_YD_BASE + 0 && PIN_YD1 == PIN_YD_BASE + 1 && PIN_YD2 == PIN_YD_BASE + 2 &&
               PIN_YD3 == PIN_YD_BASE + 3 && PIN_YD4 == PIN_YD_BASE + 4 && PIN_YD5 == PIN_YD_BASE + 5 &&
               PIN_YD6 == PIN_YD_BASE + 6 && PIN_YD7 == PIN_YD_BASE + 7,
               "YD: YD0..YD7 must be consecutive GPIOs");
/* WL: WL_CK..WL_D1, WLINK received by this chip (U1 drives clock, data 0, data 1); PIO window GPIOBASE 0 or 16 */
#define PIN_WL_BASE  29
#define PIN_WL_COUNT 3
_Static_assert(PIN_WL_CK == PIN_WL_BASE + 0 && PIN_WL_D0 == PIN_WL_BASE + 1 && PIN_WL_D1 == PIN_WL_BASE + 2,
               "WL: WL_CK..WL_D1 must be consecutive GPIOs");
/* X59_5: X59_5_CK..X59_5_D1, XLINK-59 sent by this chip (U5 drives clock, data 0, data 1); PIO window GPIOBASE 16 */
#define PIN_X59_5_BASE  32
#define PIN_X59_5_COUNT 3
_Static_assert(PIN_X59_5_CK == PIN_X59_5_BASE + 0 && PIN_X59_5_D0 == PIN_X59_5_BASE + 1 &&
               PIN_X59_5_D1 == PIN_X59_5_BASE + 2,
               "X59_5: X59_5_CK..X59_5_D1 must be consecutive GPIOs");
#define PIN_X59_TX_BASE  PIN_X59_5_BASE
#define PIN_X59_TX_COUNT PIN_X59_5_COUNT
/* X59_9: X59_9_CK..X59_9_D1, XLINK-59 received by this chip (U9 drives clock, data 0, data 1); PIO window GPIOBASE 16 */
#define PIN_X59_9_BASE  35
#define PIN_X59_9_COUNT 3
_Static_assert(PIN_X59_9_CK == PIN_X59_9_BASE + 0 && PIN_X59_9_D0 == PIN_X59_9_BASE + 1 &&
               PIN_X59_9_D1 == PIN_X59_9_BASE + 2,
               "X59_9: X59_9_CK..X59_9_D1 must be consecutive GPIOs");
#define PIN_X59_RX_BASE  PIN_X59_9_BASE
#define PIN_X59_RX_COUNT PIN_X59_9_COUNT
/* X25_5: X25_5_CK..X25_5_D1, XLINK-25 sent by this chip (U5 drives clock, data 0, data 1); PIO window GPIOBASE 16 */
#define PIN_X25_5_BASE  38
#define PIN_X25_5_COUNT 3
_Static_assert(PIN_X25_5_CK == PIN_X25_5_BASE + 0 && PIN_X25_5_D0 == PIN_X25_5_BASE + 1 &&
               PIN_X25_5_D1 == PIN_X25_5_BASE + 2,
               "X25_5: X25_5_CK..X25_5_D1 must be consecutive GPIOs");
#define PIN_X25_TX_BASE  PIN_X25_5_BASE
#define PIN_X25_TX_COUNT PIN_X25_5_COUNT
/* X25_2: X25_2_CK..X25_2_D1, XLINK-25 received by this chip (U2 drives clock, data 0, data 1); PIO window GPIOBASE 16 */
#define PIN_X25_2_BASE  41
#define PIN_X25_2_COUNT 3
_Static_assert(PIN_X25_2_CK == PIN_X25_2_BASE + 0 && PIN_X25_2_D0 == PIN_X25_2_BASE + 1 &&
               PIN_X25_2_D1 == PIN_X25_2_BASE + 2,
               "X25_2: X25_2_CK..X25_2_D1 must be consecutive GPIOs");
#define PIN_X25_RX_BASE  PIN_X25_2_BASE
#define PIN_X25_RX_COUNT PIN_X25_2_COUNT

/* ---- names shared by every chip */
#define PIN_LED PIN_LED5
#define PIN_LINK PIN_LINK_E       /* 250 ohm to the common LINK (U1-U6) */
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
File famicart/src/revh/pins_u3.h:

/* Generated by tools/fw/gen_revh_pins.py from tools/pcb/design_revh.py -- do not edit; run the script again.
 * famicart rev H, U3: /IRQ, expansion audio, CIRAM /CE + A10; sees the whole CPU bus (ZA/ZD).
 * RP2350B (QFN-80) with U13 (W25Q128JVSIQ, 16 MB) on QSPI CS0, its own 12 MHz crystal, LED D23 on LED3.
 * SWCLK (pin 33) SWCLK3, SWDIO (pin 34) SWDIO3, RUN (pin 35) nRST, USB pins 66 / 67 open.
 * "pin" below is the QFN-80 pin (design_revd.GPIO_PIN, checked against the datasheet). Include exactly one
 * pins_u<N>.h per program: the names repeat across chips with other numbers. */
#ifndef FAMICART_REVH_PINS_U3_H
#define FAMICART_REVH_PINS_U3_H

#define REVH_CHIP_3 1
#define REVH_CHIP 3
#define REVH_ROLE "x"
#define REVH_IS_HUB 0

/* ---- every connected GPIO: pin, net, what else is on the net */
#define PIN_ZA0       0  /* pin 77  ZA0: ZA1 1k -> CPU_A0 (finger 13) */
#define PIN_ZA1       1  /* pin 78  ZA1: ZA1 1k -> CPU_A1 (finger 12) */
#define PIN_ZA2       2  /* pin 79  ZA2: ZA1 1k -> CPU_A2 (finger 11) */
#define PIN_ZA3       3  /* pin 80  ZA3: ZA1 1k -> CPU_A3 (finger 10) */
#define PIN_ZA4       4  /* pin  1  ZA4: ZA2 1k -> CPU_A4 (finger 9) */
#define PIN_ZA5       5  /* pin  2  ZA5: ZA2 1k -> CPU_A5 (finger 8) */
#define PIN_ZA6       6  /* pin  3  ZA6: ZA2 1k -> CPU_A6 (finger 7) */
#define PIN_ZA7       7  /* pin  4  ZA7: ZA2 1k -> CPU_A7 (finger 6) */
#define PIN_ZA8       8  /* pin  6  ZA8: ZA3 1k -> CPU_A8 (finger 5) */
#define PIN_ZA9       9  /* pin  7  ZA9: ZA3 1k -> CPU_A9 (finger 4) */
#define PIN_ZA10     10  /* pin  8  ZA10: ZA3 1k -> CPU_A10 (finger 3) */
#define PIN_ZA11     11  /* pin  9  ZA11: ZA3 1k -> CPU_A11 (finger 2) */
#define PIN_ZA12     12  /* pin 11  ZA12: ZA4 1k -> CPU_A12 (finger 33) */
#define PIN_ZA13     13  /* pin 12  ZA13: ZA4 1k -> CPU_A13 (finger 34) */
#define PIN_ZA14     14  /* pin 13  ZA14: ZA4 1k -> CPU_A14 (finger 35) */
#define PIN_ZD0      15  /* pin 14  ZD0: ZD1 680 -> CPU_D0 (finger 43) */
#define PIN_ZD1      16  /* pin 16  ZD1: ZD1 680 -> CPU_D1 (finger 42) */
#define PIN_ZD2      17  /* pin 17  ZD2: ZD1 680 -> CPU_D2 (finger 41) */
#define PIN_ZD3      18  /* pin 18  ZD3: ZD1 680 -> CPU_D3 (finger 40) */
#define PIN_ZD4      19  /* pin 19  ZD4: ZD2 680 -> CPU_D4 (finger 39) */
#define PIN_ZD5      20  /* pin 20  ZD5: ZD2 680 -> CPU_D5 (finger 38) */
#define PIN_ZD6      21  /* pin 21  ZD6: ZD2 680 -> CPU_D6 (finger 37) */
#define PIN_ZD7      22  /* pin 22  ZD7: ZD2 680 -> CPU_D7 (finger 36) */
#define PIN_ZM2      23  /* pin 23  ZM2: ZA4 1k -> M2 (finger 32) */
#define PIN_Z_RW     24  /* pin 25  Z_RW: RN31 1k -> CPU_RW (finger 14) */
#define PIN_Z_ROMSEL 25  /* pin 26  Z_ROMSEL: RN31 1k -> nROMSEL (finger 44) */
#define PIN_LINK_C   28  /* pin 36  LINK_C: RN24 1k x4 -> LINK */
#define PIN_PWM      29  /* pin 37  PWM: RN19 1k -> AF1 */
#define PIN_IRQ_G    30  /* pin 38  IRQ_G: R21 2.2k -> GND; Q5 gate (drain nIRQ) */
#define PIN_HIRQ     31  /* pin 39  HIRQ: U6 */
#define PIN_PA10     32  /* pin 40  PA10: U2 U5; RN9 1k -> PPU_A10 (finger 53) */
#define PIN_PA11     33  /* pin 42  PA11: U2 U5; RN10 1k -> PPU_A11 (finger 54) */
#define PIN_PA12     34  /* pin 43  PA12: U2 U5; RN10 1k -> PPU_A12 (finger 55) */
#define PIN_PA13     35  /* pin 44  PA13: U2 U5; RN10 1k -> PPU_A13 (finger 56) */
#define PIN_RD_D3    36  /* pin 45  RD_D3: RN32 1k -> PPU_nRD (finger 17) */
#define PIN_NCE_D    37  /* pin 46  NCE_D: RN7 1k x2 -> CIRAM_nCE (finger 48) */
#define PIN_NA10_D   38  /* pin 47  NA10_D: RN17 1k x2 -> CIRAM_A10 (finger 18) */
#define PIN_PEV      39  /* pin 48  PEV: U2 */
#define PIN_XSTAT0   40  /* pin 49  XSTAT0: U1 */
#define PIN_XSTAT1   41  /* pin 52  XSTAT1: U1 */
#define PIN_IRQ4     42  /* pin 53  IRQ4: U4 */
#define PIN_IRQ5     43  /* pin 54  IRQ5: U5 */
#define PIN_VSEL_S   44  /* pin 55  VSEL_S: all other chips; R35 100k -> GND; Q7 gate (drain VSEL_D) */
#define PIN_LED3     45  /* pin 56  LED3: R6 2.2k -> LED3_A */

/* ---- GPIOs with no net (reset state: input buffer off, pad pull-down, isolated): 26, 27, 46, 47 */
#define REVH_UNCONNECTED_MASK 0xc0000c000000ull
/* ---- pins whose net reaches the console's card edge through the resistor arrays or a FET: 0-25, 29, 30, 32-38
 * (programs that do not serve the bus keep them inputs without pulls, docs/13 "ファームウェアの決まりと課題") */
#define REVH_CONSOLE_MASK 0x007f63ffffffull

/* ---- consecutive groups for PIO programs (in / out / set / side-set base and count). The PIO window is the
 * GPIOBASE (0 or 16) whose 32 GPIOs hold the whole group; with GPIOBASE 16, `wait gpio` numbers are relative. */
/* CPU_BUS: ZA0..Z_ROMSEL, bus capture through U3's own branch: A0-14, D0-7, M2, R/W, /ROMSEL; PIO window GPIOBASE 0 */
#define PIN_CPU_BUS_BASE  0
#define PIN_CPU_BUS_COUNT 26
_Static_assert(PIN_ZA0 == PIN_CPU_BUS_BASE + 0 && PIN_ZA1 == PIN_CPU_BUS_BASE + 1 &&
               PIN_ZA2 == PIN_CPU_BUS_BASE + 2 && PIN_ZA3 == PIN_CPU_BUS_BASE + 3 &&
               PIN_ZA4 == PIN_CPU_BUS_BASE + 4 && PIN_ZA5 == PIN_CPU_BUS_BASE + 5 &&
               PIN_ZA6 == PIN_CPU_BUS_BASE + 6 && PIN_ZA7 == PIN_CPU_BUS_BASE + 7 &&
               PIN_ZA8 == PIN_CPU_BUS_BASE + 8 && PIN_ZA9 == PIN_CPU_BUS_BASE + 9 &&
               PIN_ZA10 == PIN_CPU_BUS_BASE + 10 && PIN_ZA11 == PIN_CPU_BUS_BASE + 11 &&
               PIN_ZA12 == PIN_CPU_BUS_BASE + 12 && PIN_ZA13 == PIN_CPU_BUS_BASE + 13 &&
               PIN_ZA14 == PIN_CPU_BUS_BASE + 14 && PIN_ZD0 == PIN_CPU_BUS_BASE + 15 &&
               PIN_ZD1 == PIN_CPU_BUS_BASE + 16 && PIN_ZD2 == PIN_CPU_BUS_BASE + 17 &&
               PIN_ZD3 == PIN_CPU_BUS_BASE + 18 && PIN_ZD4 == PIN_CPU_BUS_BASE + 19 &&
               PIN_ZD5 == PIN_CPU_BUS_BASE + 20 && PIN_ZD6 == PIN_CPU_BUS_BASE + 21 &&
               PIN_ZD7 == PIN_CPU_BUS_BASE + 22 && PIN_ZM2 == PIN_CPU_BUS_BASE + 23 &&
               PIN_Z_RW == PIN_CPU_BUS_BASE + 24 && PIN_Z_ROMSEL == PIN_CPU_BUS_BASE + 25,
               "CPU_BUS: ZA0..Z_ROMSEL must be consecutive GPIOs");
/* ZA: ZA0..ZA14, to CPU_A0..CPU_A14 through ZA1, ZA2, ZA3, ZA4 (1k each); PIO window GPIOBASE 0 */
#define PIN_ZA_BASE  0
#define PIN_ZA_COUNT 15
_Static_assert(PIN_ZA0 == PIN_ZA_BASE + 0 && PIN_ZA1 == PIN_ZA_BASE + 1 && PIN_ZA2 == PIN_ZA_BASE + 2 &&
               PIN_ZA3 == PIN_ZA_BASE + 3 && PIN_ZA4 == PIN_ZA_BASE + 4 && PIN_ZA5 == PIN_ZA_BASE + 5 &&
               PIN_ZA6 == PIN_ZA_BASE + 6 && PIN_ZA7 == PIN_ZA_BASE + 7 && PIN_ZA8 == PIN_ZA_BASE + 8 &&
               PIN_ZA9 == PIN_ZA_BASE + 9 && PIN_ZA10 == PIN_ZA_BASE + 10 && PIN_ZA11 == PIN_ZA_BASE + 11 &&
               PIN_ZA12 == PIN_ZA_BASE + 12 && PIN_ZA13 == PIN_ZA_BASE + 13 && PIN_ZA14 == PIN_ZA_BASE + 14,
               "ZA: ZA0..ZA14 must be consecutive GPIOs");
/* ZD: ZD0..ZD7, to CPU_D0..CPU_D7 through ZD1, ZD2 (680 each); PIO window GPIOBASE 0 */
#define PIN_ZD_BASE  15
#define PIN_ZD_COUNT 8
_Static_assert(PIN_ZD0 == PIN_ZD_BASE + 0 && PIN_ZD1 == PIN_ZD_BASE + 1 && PIN_ZD2 == PIN_ZD_BASE + 2 &&
               PIN_ZD3 == PIN_ZD_BASE + 3 && PIN_ZD4 == PIN_ZD_BASE + 4 && PIN_ZD5 == PIN_ZD_BASE + 5 &&
               PIN_ZD6 == PIN_ZD_BASE + 6 && PIN_ZD7 == PIN_ZD_BASE + 7,
               "ZD: ZD0..ZD7 must be consecutive GPIOs");
/* CIRAM: PA10..NA10_D, CIRAM table: in PA10-13 and /RD, side-set /CE and A10 (docs/13: in_base 32, side-set 37 / 38); PIO window GPIOBASE 16 */
#define PIN_CIRAM_BASE  32
#define PIN_CIRAM_COUNT 7
_Static_assert(PIN_PA10 == PIN_CIRAM_BASE + 0 && PIN_PA11 == PIN_CIRAM_BASE + 1 &&
               PIN_PA12 == PIN_CIRAM_BASE + 2 && PIN_PA13 == PIN_CIRAM_BASE + 3 &&
               PIN_RD_D3 == PIN_CIRAM_BASE + 4 && PIN_NCE_D == PIN_CIRAM_BASE + 5 &&
               PIN_NA10_D == PIN_CIRAM_BASE + 6,
               "CIRAM: PA10..NA10_D must be consecutive GPIOs");
/* PA10_13: PA10..PA13, to PPU_A10..PPU_A13 through RN9, RN10 (1k each); PIO window GPIOBASE 16 */
#define PIN_PA10_13_BASE  32
#define PIN_PA10_13_COUNT 4
_Static_assert(PIN_PA10 == PIN_PA10_13_BASE + 0 && PIN_PA11 == PIN_PA10_13_BASE + 1 &&
               PIN_PA12 == PIN_PA10_13_BASE + 2 && PIN_PA13 == PIN_PA10_13_BASE + 3,
               "PA10_13: PA10..PA13 must be consecutive GPIOs");
/* XSTAT: XSTAT0..XSTAT1, shared with U1; PIO window GPIOBASE 16 */
#define PIN_XSTAT_BASE  40
#define PIN_XSTAT_COUNT 2
_Static_assert(PIN_XSTAT0 == PIN_XSTAT_BASE + 0 && PIN_XSTAT1 == PIN_XSTAT_BASE + 1,
               "XSTAT: XSTAT0..XSTAT1 must be consecutive GPIOs");
/* IRQ4_5: IRQ4..IRQ5, shared with U4, U5; PIO window GPIOBASE 16 */
#define PIN_IRQ4_5_BASE  42
#define PIN_IRQ4_5_COUNT 2
_Static_assert(PIN_IRQ4 == PIN_IRQ4_5_BASE + 0 && PIN_IRQ5 == PIN_IRQ4_5_BASE + 1,
               "IRQ4_5: IRQ4..IRQ5 must be consecutive GPIOs");

/* ---- names shared by every chip */
#define PIN_LED PIN_LED3
#define PIN_LINK PIN_LINK_C       /* 250 ohm to the common LINK (U1-U6) */

#endif /* FAMICART_REVH_PINS_U3_H */
